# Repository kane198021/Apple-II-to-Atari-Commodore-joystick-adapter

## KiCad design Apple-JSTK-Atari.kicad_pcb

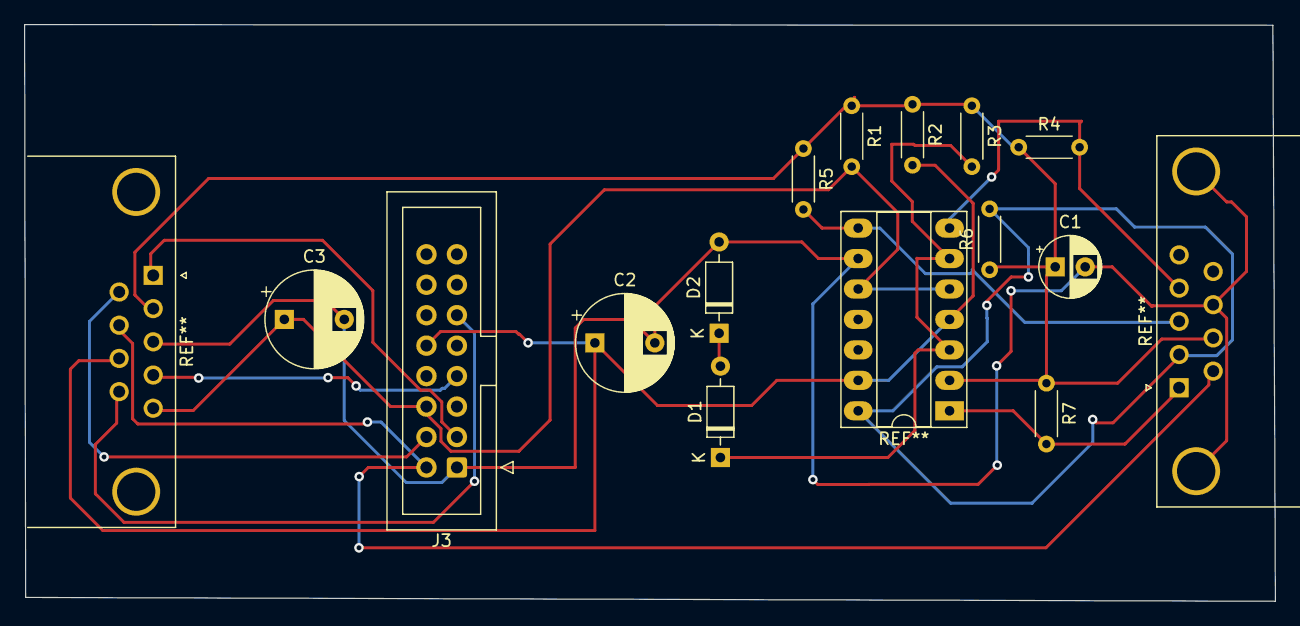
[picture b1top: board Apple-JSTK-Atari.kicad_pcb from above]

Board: 2 copper layers, 104.3 x 48.1 mm, 13 parts (0 on the bottom side), 5 nets.

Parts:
C1: 4.5uF; CP_Radial_D5.0mm_P2.50mm
C2, C3: .01uF; CP_Radial_D8.0mm_P5.00mm
D1, D2: 1N914; D_DO-35_SOD27_P7.62mm_Horizontal
J3: Conn_02x08_Counter_Clockwise; IDC-Header_2x08_P2.54mm_Vertical
R1, R2: 220K; R_Axial_DIN0204_L3.6mm_D1.6mm_P5.08mm_Horizontal
R3, R4, R5, R6, R7: 1K; R_Axial_DIN0204_L3.6mm_D1.6mm_P5.08mm_Horizontal

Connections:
/+5V: C1.1, R1.1, R2.1, R3.1, R4.1, R5.1, R6.1, R7.1
/GND: C1.2, C2.2, C3.2, D2.2 (A), J3.1
/Joystick1_X-Axis: C3.1, J3.6, R1.2
/Joystick1_Y-Axis: C2.1, J3.10, R2.2
unnamed: D1.1 (K), R3.2
